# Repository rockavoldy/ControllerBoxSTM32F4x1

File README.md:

# ControllerBox STM32F4x1 EMCPro

This repository have the source file of my ControllerBox STM32F4x1 with EMCFFB Pro Firmware. You can use this PCB design source as you like, i will really grateful if you link to this repository.

# Libraries used
- [piit79/Kicad-STM32](https://github.com/piit79/Kicad-STM32)

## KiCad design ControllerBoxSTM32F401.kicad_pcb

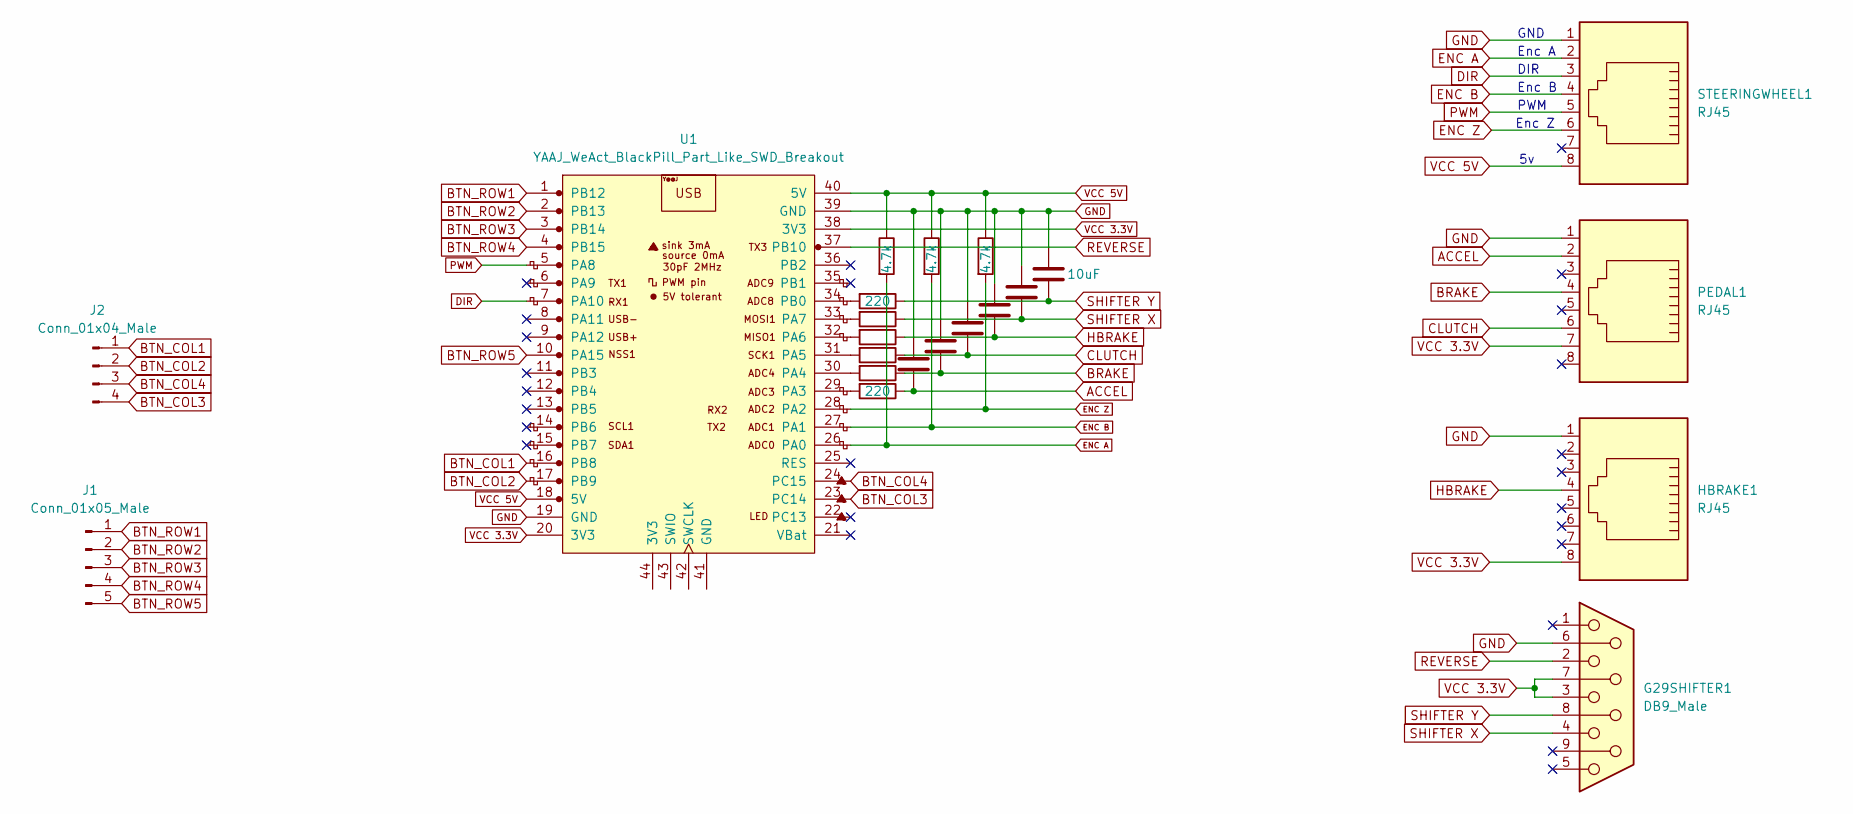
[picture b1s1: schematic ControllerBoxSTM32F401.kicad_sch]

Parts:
C1, C2, C3, C4, C5, C6: 10uF; C_0805_2012Metric_Pad1.18x1.45mm_HandSolder
G29SHIFTER1: DB9_Male; DSUB-9_Male_Horizontal_P2.77x2.84mm_EdgePinOffset7.70mm_Hou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
HBRAKE1: RJ45; RJ45_Amphenol_RJHSE538X
J1: Conn_01x05_Male; JST_XH_B5B-XH-A_1x05_P2.50mm_Vertical
J2: Conn_01x04_Male; JST_XH_B4B-XH-A_1x04_P2.50mm_Vertical
PEDAL1: RJ45; RJ45_Amphenol_RJHSE538X
R1, R2, R3: 4.7k; R_0805_2012Metric_Pad1.20x1.40mm_HandSolder
R4, R5, R6, R7, R8, R9: 220; R_0805_2012Metric_Pad1.20x1.40mm_HandSolder
STEERINGWHEEL1: RJ45; RJ45_Amphenol_RJHSE538X
U1: YAAJ_WeAct_BlackPill_Part_Like_SWD_Breakout; YAAJ_WeAct_BlackPill_2

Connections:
ACCEL: C1.1, PEDAL1.2, R4.1
BRAKE: C2.2, PEDAL1.4, R5.1
BTN_COL1: J2.1, U1.16 (PB8)
BTN_COL2: J2.2, U1.17 (PB9)
BTN_COL3: J2.4, U1.23 (PC14)
BTN_COL4: J2.3, U1.24 (PC15)
BTN_ROW1: J1.1, U1.1 (PB12)
BTN_ROW2: J1.2, U1.2 (PB13)
BTN_ROW3: J1.3, U1.3 (PB14)
BTN_ROW4: J1.4, U1.4 (PB15)
BTN_ROW5: J1.5, U1.10 (PA15)
CLUTCH: C3.2, PEDAL1.6, R6.1
DIR: STEERINGWHEEL1.3, U1.7 (PA10)
ENC A: R1.2, STEERINGWHEEL1.2, U1.26 (PA0)
ENC B: R2.2, STEERINGWHEEL1.4, U1.27 (PA1)
ENC Z: R3.2, STEERINGWHEEL1.6, U1.28 (PA2)
GND: C1.2, C2.1, C3.1, C4.1, C5.1, C6.1, G29SHIFTER1.6, HBRAKE1.1, PEDAL1.1, STEERINGWHEEL1.1, U1.19 (GND), U1.39 (GND)
HBRAKE: C4.2, HBRAKE1.4, R7.1
unnamed: R4.2, U1.29 (PA3)
unnamed: R5.2, U1.30 (PA4)
unnamed: R6.2, U1.31 (PA5)
unnamed: R7.2, U1.32 (PA6)
unnamed: R8.2, U1.33 (PA7)
unnamed: R9.2, U1.34 (PB0)
PWM: STEERINGWHEEL1.5, U1.5 (PA8)
REVERSE: G29SHIFTER1.2, U1.37 (PB10)
SHIFTER X: C5.2, G29SHIFTER1.4, R8.1
SHIFTER Y: C6.2, G29SHIFTER1.8, R9.1
VCC 3.3V: G29SHIFTER1.3, G29SHIFTER1.7, HBRAKE1.8, PEDAL1.7, U1.20 (3V3), U1.38 (3V3)
VCC 5V: R1.1, R2.1, R3.1, STEERINGWHEEL1.8, U1.18 (5V), U1.40 (5V)

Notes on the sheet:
Enc A
PWM
DIR
GND
Enc Z
Enc B

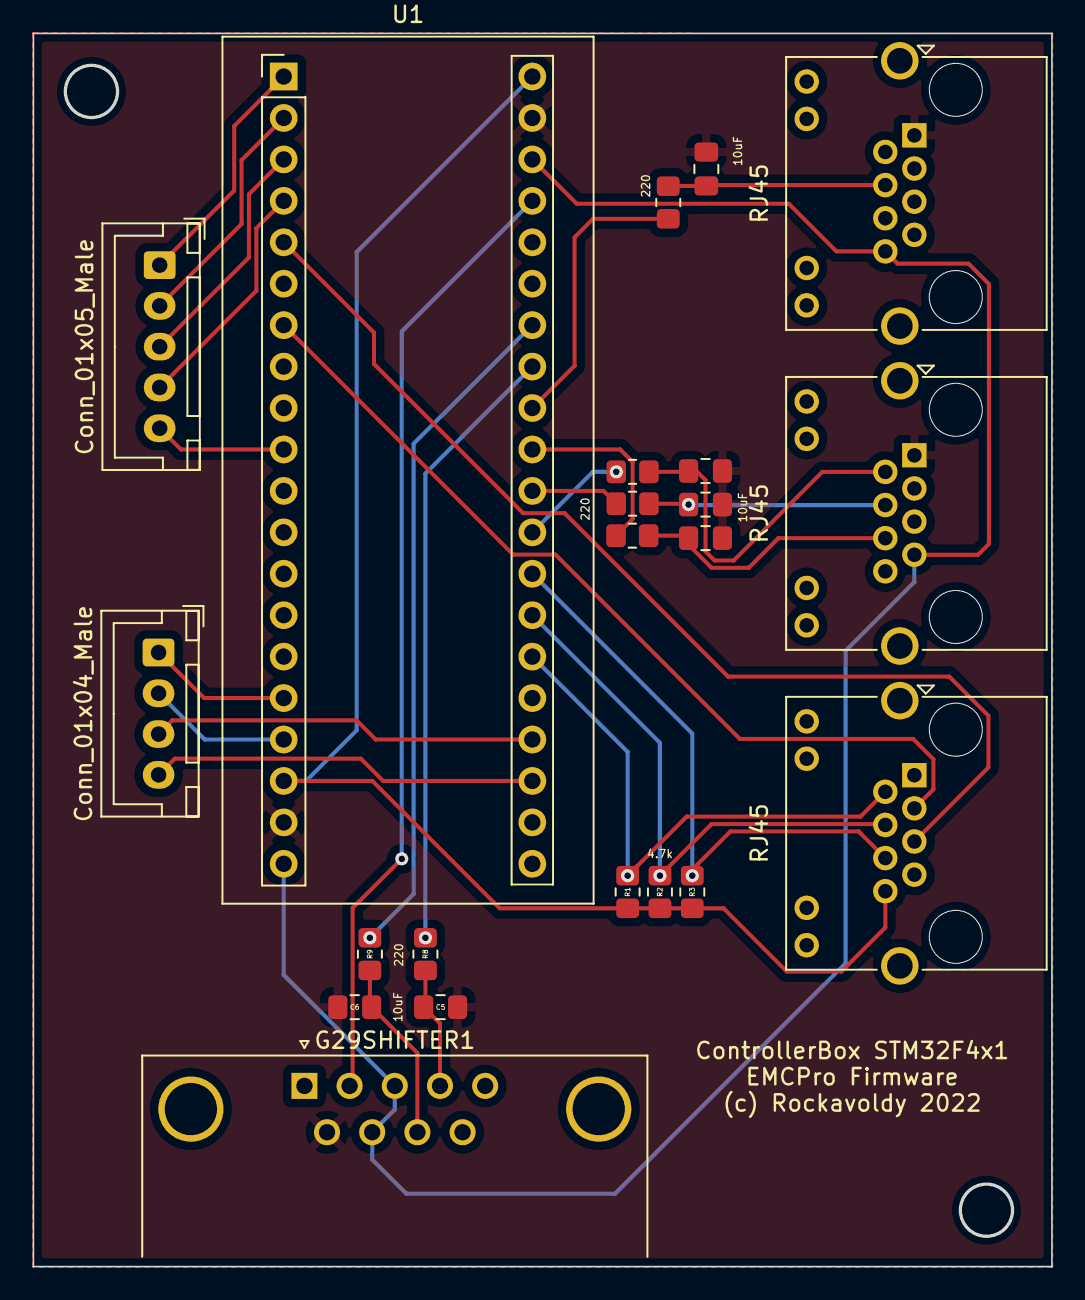
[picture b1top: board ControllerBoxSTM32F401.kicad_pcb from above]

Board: 2 copper layers, 62.3 x 75.5 mm, 22 parts (0 on the bottom side), 30 nets.

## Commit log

2022-02-22 update PCB and create edge cuts
2022-02-22 add button matrix to PCB
2022-03-10 fix v1 and make it smaller
2022-03-12 change component to SMD, and lowering the footprint to <100mm
2022-03-30 update pcb production
2022-05-18 add readme; fix wrong pin issue for G29Shifter
2022-06-05 Create LICENSE
